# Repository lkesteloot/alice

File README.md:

# Alice website

Hardware projects from the 1990s and our revival and redesign starting in 2015 of that project and projects inspired by it. See the [web page](http://lkesteloot.github.io/alice/).

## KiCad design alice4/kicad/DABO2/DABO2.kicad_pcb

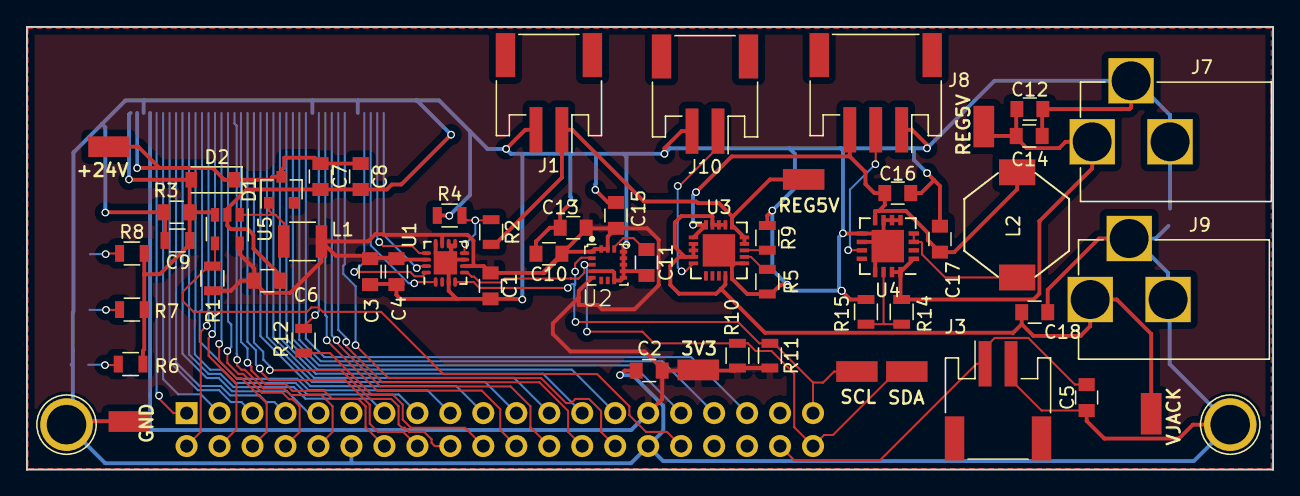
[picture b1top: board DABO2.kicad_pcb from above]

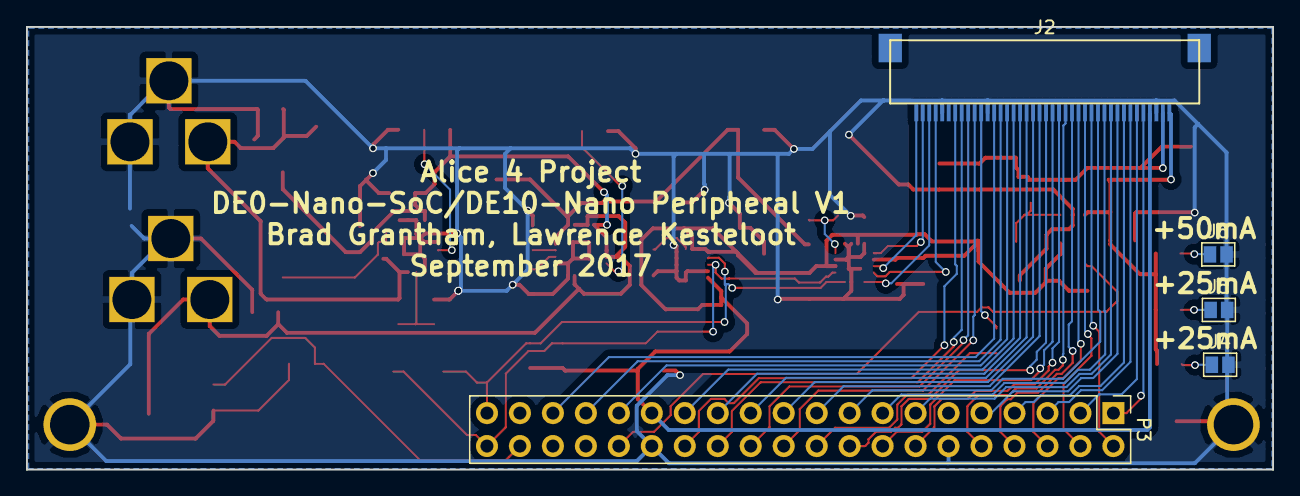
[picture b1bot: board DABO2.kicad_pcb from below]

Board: 2 copper layers, 96.0 x 34.1 mm, 62 parts (5 on the bottom side), 58 nets.

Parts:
C1, C3, C5, C9, C17: .1uF; C_0805
C2, C6, C15, C16, C18: 10uF; C_0805
C4, C7, C8: 1uF; C_0805
C10, C13: 100nF; C_0805
C11: 10nF; C_0805
C12: 2.2uF; C_0805
C14: 100uF; C_0805
D1: BAT54; SOT-23
D2: MM3Z24VT1G; D_SOD-123
HOLE0, HOLE1: MountingHole_2-5mm; 1pin
J1: LIPO; JST_PH_S2B-PH-SM4-TB_02x2.00mm_Angled
J2: LCD; kyocera_6288
J3: HOME; JST_PH_S2B-PH-SM4-TB_02x2.00mm_Angled
J4, J5: +25mA; GS2
J6: +50mA; GS2
J7: 5VOUT; BARREL_JACK
J8: PWRSW; JST_PH_S3B-PH-SM4-TB_03x2.00mm_Angled
J9: 5VIN; BARREL_JACK
J10: THERM; JST_PH_S2B-PH-SM4-TB_02x2.00mm_Angled
L1: 10uH; R_1210
L2: 6.8uH; inductor_8mm_8mm_smt
P3: GPIO0; Pin_Header_Straight_2x20_Pitch2.54mm
R1: 10K; R_0805
R2, R4, R15: 200K; R_0805
R3, R6, R7: 12; R_0805
R5: 100K; R_0805
R8: 6; R_0805
R9: 1K; R_0805
R10, R11: 2.2K; R_0805
R12: 22; R_0805
R14: 1.87M; R_0805
TP1: GND; testpoint_smd_1206
TP2: 3V3; testpoint_smd_1206
TP3: 5VIN; testpoint_smd_1206
TP4: LED-A; testpoint_smd_1206
TP5: LIPO; testpoint_smd_1206
TP6: 5VOUT; testpoint_smd_1206
TP7: SDA; testpoint_smd_1206
TP8: SCL; testpoint_smd_1206
U1: stmpe811; QFN-16-1EP_3x3mm_Pitch0.5mm
U2: l3gd20h
U3: mcp73871; QFN-20-1EP_4x4mm_Pitch0.5mm
U4: tps61090rsar; QFN-16-1EP_4x4mm_Pitch0.65mm
U5: fan5333bsx; SOT-23-5

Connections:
+3V3: C1.1, C2.1, C3.1, C4.1, C6.1, C10.2, C13.1, C15.1, J2.4, L1.1, P3.29, R1.2, R10.2, R11.2, TP2.1, U1.6, U1.11, U1.14, U2.1, U2.5, U2.15, U2.16, U5.5
B0: J2.21, P3.19
B1: J2.22, P3.21
B2: J2.23, P3.23
B3: J2.24, P3.25
B4: J2.25, P3.27
B5: J2.26, P3.31
B6: J2.27, P3.33
B7: J2.28, P3.35
BACKLIGHT_PWM: P3.32, R1.1, U5.4
DATA_ENABLE: J2.34, P3.28
DISPLAY_ON: J2.31, P3.22
G0: J2.13, P3.2
G1: J2.14, P3.4
G2: J2.15, P3.6
G3: J2.16, P3.8
G4: J2.17, P3.10
G5: J2.18, P3.14
G6: J2.19, P3.16
G7: J2.20, P3.18
GND: C1.2, C2.2, C3.2, C4.2, C5.1, C6.2, C7.2, C8.2, C9.2, C10.1, C11.2, C12.2, C13.2, C14.2, C15.2, C16.2, C17.2, C18.2, HOLE0.1, HOLE1.1, J1.2, J2.3, J2.29, J2.36, J3.2, J4.2, J5.2, J6.2, J7.2, J7.3, J8.1, J9.2, J9.3, J10.2, P3.12, P3.30, R3.1, R4.1, R5.1, R9.1, R15.1, TP1.1, U1.3, U1.7, U1.9, U1.10, U1.12, U1.17, U2.4, U2.8, U2.9, U2.10, U2.11, U2.12, U2.13, U3.10, U3.11, U3.21, U4.5, U4.6, U4.7, U4.9, U4.10, U4.13, U4.17, U5.2
HOME: C5.2, J3.1, P3.38
HSYNC: J2.32, P3.24
LCD_CLK: P3.20, R12.2
LED-A: C7.1, C8.1, D1.3, D2.1, J2.2, TP4.1
LED-K: C9.1, D2.2, J2.1, R3.2, R6.2, R7.2, R8.2, U5.3
LIPO: J1.1, R2.2, TP5.1, U3.14, U3.15, U3.16
unnamed: C11.1, U2.14
unnamed: D1.1, L1.2, U5.1
unnamed: J2.30, R12.1
unnamed: J4.1, R6.1
unnamed: J5.1, R7.1
unnamed: J6.1, R8.1
unnamed: J10.1, U3.5
unnamed: L2.2, U4.3, U4.4
unnamed: R2.1, R4.2, U1.8
unnamed: R5.2, U3.12
unnamed: R9.2, U3.13
unnamed: R14.1, R15.2, U4.14
PWREN: J8.2, U4.11
R0: J2.5, P3.1
R1: J2.6, P3.3
R2: J2.7, P3.5
R3: J2.8, P3.7
R4: J2.9, P3.9
R5: J2.10, P3.13
R6: J2.11, P3.15
R7: J2.12, P3.17
REGULATED5V: C12.1, C14.1, J7.1, R14.2, TP6.1, U4.1, U4.15, U4.16
SCL: P3.39, R11.1, TP8.1, U1.4, U2.2
SDA: P3.40, R10.1, TP7.1, U1.5, U2.3
VBAT: C16.1, C17.1, J8.3, L2.1, U3.1, U3.20, U4.8
VJACK: C18.1, J9.1, TP3.1, U3.2, U3.3, U3.4, U3.9, U3.17, U3.18, U3.19
VSYNC: J2.33, P3.26
XL: J2.39, U1.13
XR: J2.37, U1.16
YD: J2.38, U1.1
YU: J2.40, U1.15

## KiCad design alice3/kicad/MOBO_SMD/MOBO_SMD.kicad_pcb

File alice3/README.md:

# Alice III

This is the third model of the Alice machine. It runs a silicon Z80 with
two co-processors: an ARM for keyboard, disk, and serial port, and a Propeller for video.

The 80MHz Propeller has 48K of internal RAM, drives VGA and the 5-pin Aux connector (intended for audio but wired generically to 3 Propeller pins) and thus provides opportunities for video and other experimentation.

The 168MHz STM32F415 ARM Cortex-M4 contains 192K of RAM and is connected to a PS/2 port, an SD card, and a simple UART on a 2-pin header, and has a firmware monitor that can be altered or replaced.

In the `kicad` directory are various schematics and PCBs. The latest is
`MOBO_SMD`, which uses surface mount versions of the parts.

To bring up a new board:

* Power:
    * Use a wall wart to provide micro-USB power. Verify that the D2 LED
      (closest to the switches) is on.  If you have an in-line USB
      current meter, there should be less than 10 mA being initially pulled.
      (More is pulled later when the board is fully brought up.)
* Propeller:
    * Hook up the Prop Plug. The Vss pin should be closest to the corner of
      the board.
    * Run PropellerIDE, load the `video_board/propeller/Main.spin` file,
      and program the EEPROM. After this you should be able to hook up a VGA
      monitor and see the line `Alice 3 GPU firmware`.
    * Remove the Prop Plug.
* Cortex-M4:
    * Connect your computer to the USB jack of the Alice III.
    * Short the header closest to the ARM, labeled "JP1".
    * Hard-reset the board (the push button closest to the LEDs).
    * Wait one second, then remove the jumper.  If you look in your
      USB device list, you should see the STM bootloader.  For example,
      on MacOS X, the output of `system_profiler SPUSBDataType` should
      contain a section similar to:
```
        STM32  BOOTLOADER:

          Product ID: 0xdf11
          Vendor ID: 0x0483  (STMicroelectronics)
          Version: 22.00
          Serial Number: 366A34573335
          Speed: Up to 12 Mb/sec
          Manufacturer: STMicroelectronics
          Location ID: 0x14100000 / 20
          Current Available (mA): 1000
          Current Required (mA): 100
          Extra Operating Current (mA): 0
```
    * In `binaries`, run `sh install_cortex_m4_firmware.sh`.
        * `dfu-util` is a prerequisite.  It can be installed
	  on MacOS (our primary platform) through MacPorts, or you
	  can compile it from the source at
          `git://git.code.sf.net/p/dfu-util/dfu-util`.
    * To interact with the boot monitor:
        * Locate the 2-pin header closest to the MicroSD socket.
          There's no label on this header.
        * Attach a serial transceiver to this header; transmit to the pin
          closest to the ARM, and receive from the other pin.
          E.g. connect FTDI Tx to the pin closer to the ARM and
          FTDI Rx to the pin further from the ARM.
        * Connect to the serial port at 115200 baud.
        * When you hard-reset or power-on the Alice III, you should see
          on the serial port "Alice 3 I/O firmware" followed by the
          firmware build date.
* Z80:
    * Format a MicroSD card for FAT32.
    * Copy `binaries/bootrom.bin`, `binaries/boot.dsk` and `binaries/disks.txt` to the MicroSD card.
    * Install the MicroSD card in the Alice III and power-on or hard-reset the Alice III.

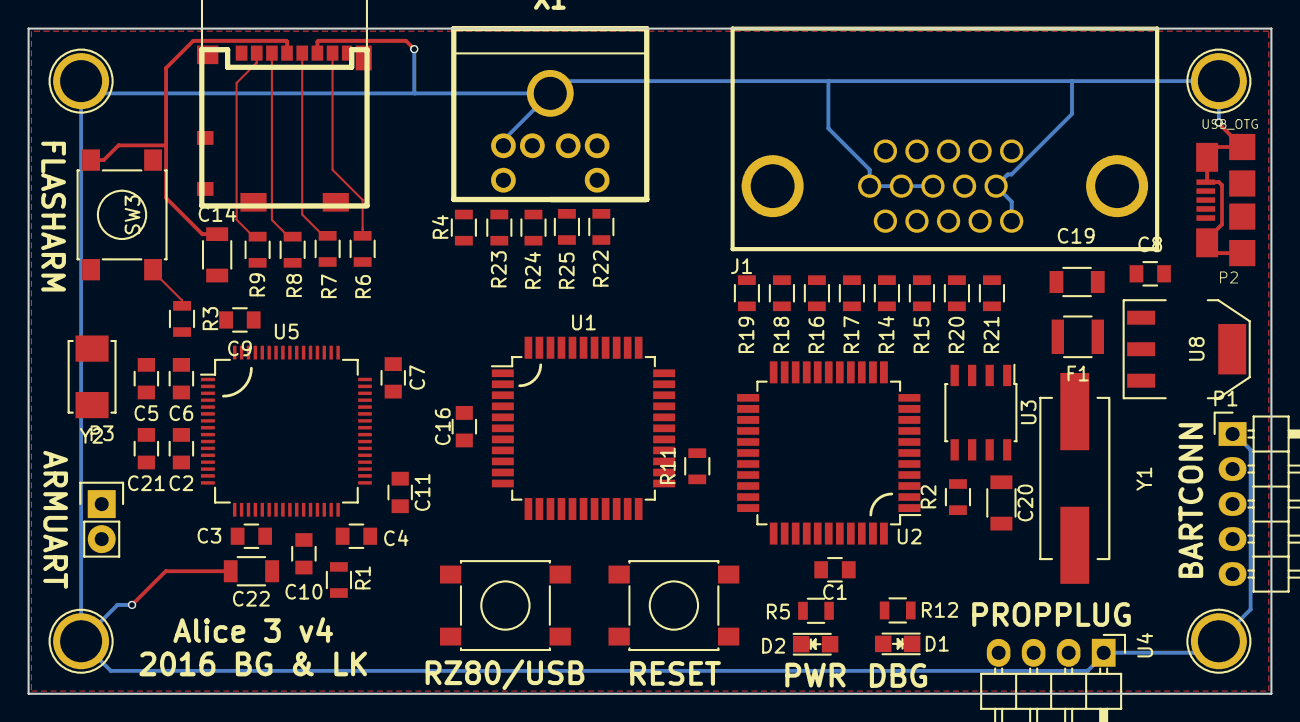
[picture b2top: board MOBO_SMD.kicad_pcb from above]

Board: 2 copper layers, 90.2 x 48.3 mm, 64 parts (0 on the bottom side), 86 nets.

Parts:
C1, C16: 0.1 µF; C_0805
C2, C3, C4, C7, C8, C9: 100nF; C_0805
C5, C6: 22pF; C_0805
C10, C11: 2.2µF; C_0805
C14, C19, C20: 10µF; C_1206
C21: 1µ; C_0805
C22: 4.7µ; C_1206
CON1: MicroSD; microsd_1040310811
D1: DEBUG LED; LED-0805
D2: POWER; LED_0805
F1: F_Small; R_1210
HOLE0, HOLE1, HOLE2, HOLE3: 1pin
J1: VGA; 00JG-DB15HDSOCKET
P1: CONN_01X05; Pin_Header_Angled_1x05
P2: USB_OTG; 10118192-0001LF
P3: UART1; Pin_Header_Straight_1x02
R1, R2, R3, R11: 10k; R_0805
R4: 220; R_0805
R5, R12, R24, R25: 100; R_0805
R6, R7, R8, R9: 68K; R_0805
R14, R16, R18, R20, R21: 240; R_0805
R15, R17, R19: 470; R_0805
R22, R23: 10K; R_0805
SW1: RESET; SW_SPST_PTS645
SW2: SOFT RESET; SW_SPST_PTS645
SW3: FLASH ARM; SW_SPST_PTS645
U1: Z80CPU-SMD; LQFP-44_10x10mm_Pitch0.8mm
U2: Propeller_P8X32A-Q44; LQFP-44_10x10mm_Pitch0.8mm
U3: 24LC256; SOIC-8_3.9x4.9mm_Pitch1.27mm
U4: Propeller_Plug; Pin_Header_Angled_1x04
U5: STM32F415RG; LQFP-64_10x10mm_Pitch0.5mm
U8: LD29080DT33R; SOT-223
X1: MINI_DIN_6; cui-md-60s
Y1: 5 MHz; Crystal_HC49-SD_SMD
Y2: 16MHz; ABM3

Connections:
+3V3: C1.1, C2.2, C3.2, C4.2, C7.2, C9.2, C14.1, C16.1, C20.1, C21.2, C22.2, CON1.4, D2.2, P1.2, R2.1, R6.1, R7.1, R8.1, R9.1, SW2.2, SW3.2, U1.6, U1.12, U1.13, U2.8, U2.18, U2.30, U2.40, U3.8, U5.1, U5.13, U5.19, U5.32, U5.48, U5.64, U8.3
+5V: C8.2, C19.1, F1.2, J1.9, R4.2, R22.2, R23.2, U8.1, X1.4
/IO/CS: CON1.2, R9.2, U5.41
/IO/DI: CON1.3, R8.2, U5.36
/IO/DO: CON1.7, R6.2, U5.35
/IO/SCK: CON1.5, R7.2, U5.34
A0: U1.27, U2.31, U5.8
A1: U1.28, U2.32, U5.9
A2: U1.29, U2.33, U5.10
A3: U1.30, U5.11
A4: U1.31, U5.24
A5: U1.32, U5.25
A6: U1.34, U5.37
A7: U1.35, U2.1, U5.38
A8: U1.36, U5.39
A9: U1.37, U5.40
A10: U1.38, U5.51
A11: U1.40, U5.52
A12: U1.41, U5.53
A13: U1.42, U5.2
A14: U1.43, U5.3
A15: U1.44, U5.4
CLK: U1.1, U2.2
D0: U1.9, U2.19, U5.14
D1: U1.10, U2.20, U5.15
D2: U1.7, U2.21, U5.16
D3: U1.3, U2.22, U5.17
D4: U1.2, U2.23, U5.20
D5: U1.4, U2.24, U5.21
D6: U1.5, U2.25, U5.22
D7: U1.8, U2.26, U5.23
GND: C1.2, C2.1, C3.1, C4.1, C5.2, C6.1, C7.1, C8.1, C9.1, C10.2, C11.2, C14.2, C16.2, C19.2, C20.2, C21.1, C22.1, CON1.6, D1.1, HOLE0.1, HOLE1.1, HOLE2.1, HOLE3.1, J1.5, J1.6, J1.7, J1.8, J1.10, P1.1, P2.5, P2.6, R1.2, R3.2, R5.2, R11.2, SW1.2, U1.26, U2.5, U2.6, U2.17, U2.27, U2.39, U3.1, U3.2, U3.3, U3.4, U3.7, U4.1, U5.12, U5.18, U5.63, U8.2, X1.3, X1.GND
KBD_CLK: R24.1, U5.30
KBD_DATA: R25.1, U5.33
unnamed: C5.1, U5.5, Y2.1
unnamed: C6.2, U5.6, Y2.2
unnamed: C10.1, U5.31
unnamed: C11.1, U5.47
unnamed: D1.2, R12.2
unnamed: D2.1, R5.1
unnamed: F1.1, P2.1
unnamed: J1.1, R18.1, R19.1
unnamed: J1.2, R16.1, R17.1
unnamed: J1.3, R14.1, R15.1
unnamed: J1.13, R21.2
unnamed: J1.14, R20.2
unnamed: P1.3, U2.34
unnamed: P1.4, U2.4
unnamed: P1.5, U2.3
unnamed: P3.1, U5.58
unnamed: P3.2, U5.59
unnamed: R1.1, R12.1, U5.28
unnamed: R2.2, U2.36, U3.5
unnamed: R3.1, SW3.1, U5.60
unnamed: R22.1, R25.2, X1.1
unnamed: R23.1, R24.2, X1.5
unnamed: SW2.1, U5.57
unnamed: U2.28, Y1.1
unnamed: U2.29, Y1.2
unnamed: U2.35, U3.6
unnamed: U2.37, U4.4
unnamed: U2.38, U4.3
USB_DET: R4.1, U5.42
USB_D_N: P2.2, U5.44
USB_D_P: P2.3, U5.45
USB_ID: P2.4, U5.43
VGA_B0: R15.2, U2.11
VGA_B1: R14.2, U2.12
VGA_G0: R17.2, U2.13
VGA_G1: R16.2, U2.14
VGA_HSYNC: R21.1, U2.10
VGA_R0: R19.2, U2.16
VGA_R1: R18.2, U2.15
VGA_VSYNC: R20.1, U2.9
~BUSACK: U1.20, U5.62
~BUSRQ: U1.22, U5.29
~HALT: U1.14, U5.50
~IORQ: U1.16, U2.42, U5.26
~MREQ: U1.15, U5.27
~PROP_READY~: U2.41, U5.46
~RD: U1.18, U2.44, U5.55
~RESET: SW1.1, U2.7, U4.2, U5.7
~RFSH: U1.25, U5.49
~WAIT: U1.21, U5.54
~WR: U1.19, U2.43, U5.56
~Z80_RESET: R11.1, U1.23, U5.61

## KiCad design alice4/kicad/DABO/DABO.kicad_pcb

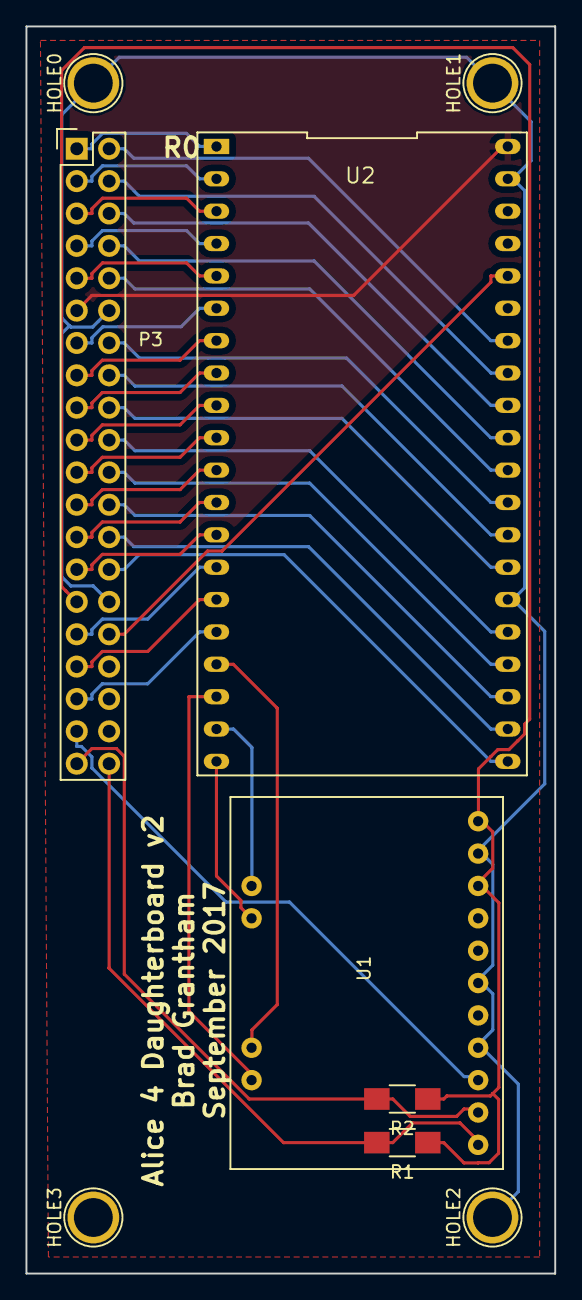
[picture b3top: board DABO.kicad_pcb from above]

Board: 2 copper layers, 41.5 x 97.9 mm, 9 parts (0 on the bottom side), 40 nets.

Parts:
HOLE0, HOLE1, HOLE2, HOLE3: 1pin
P3: CONN_02X20; Pin_Header_Straight_2x20
R1, R2: 3.3; R_1206_HandSoldering
U1: touchscreen_controller; Adafruit_STMPE610
U2: LCDBREAKOUT; DIP-40_1_ELL

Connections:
+3V3: P3.29, R1.1, R2.1, U1.13, U1.15
+5V: P3.11, U2.40
B0: P3.19, U2.9
B1: P3.21, U2.10
B2: P3.23, U2.11
B3: P3.25, U2.12
B4: P3.27, U2.13
B5: P3.31, U2.14
B6: P3.33, U2.15
B7: P3.35, U2.16
BACKLIGHT_PWM: P3.32, U2.36
DATA_ENABLE: P3.28, U2.21
DISPLAY_ON: P3.22, U2.24
G0: P3.2, U2.34
G1: P3.4, U2.33
G2: P3.6, U2.32
G3: P3.8, U2.31
G4: P3.10, U2.30
G5: P3.14, U2.29
G6: P3.16, U2.28
G7: P3.18, U2.27
GND: HOLE0.1, HOLE1.1, HOLE2.1, HOLE3.1, P3.12, P3.30, U1.8, U1.10, U1.14, U2.26, U2.39
HSYNC: P3.24, U2.23
INT: P3.37, U1.7
LCD_CLK: P3.20, U2.25
R0: P3.1, U2.1
R1: P3.3, U2.2
R2: P3.5, U2.3
R3: P3.7, U2.4
R4: P3.9, U2.5
R5: P3.13, U2.6
R6: P3.15, U2.7
R7: P3.17, U2.8
SCL: P3.39, R2.2, U1.6
SDA: P3.40, R1.2, U1.5
VSYNC: P3.26, U2.22
X+: U1.1, U2.19
X-: U1.3, U2.17
Y+: U1.2, U2.20
Y-: U1.4, U2.18

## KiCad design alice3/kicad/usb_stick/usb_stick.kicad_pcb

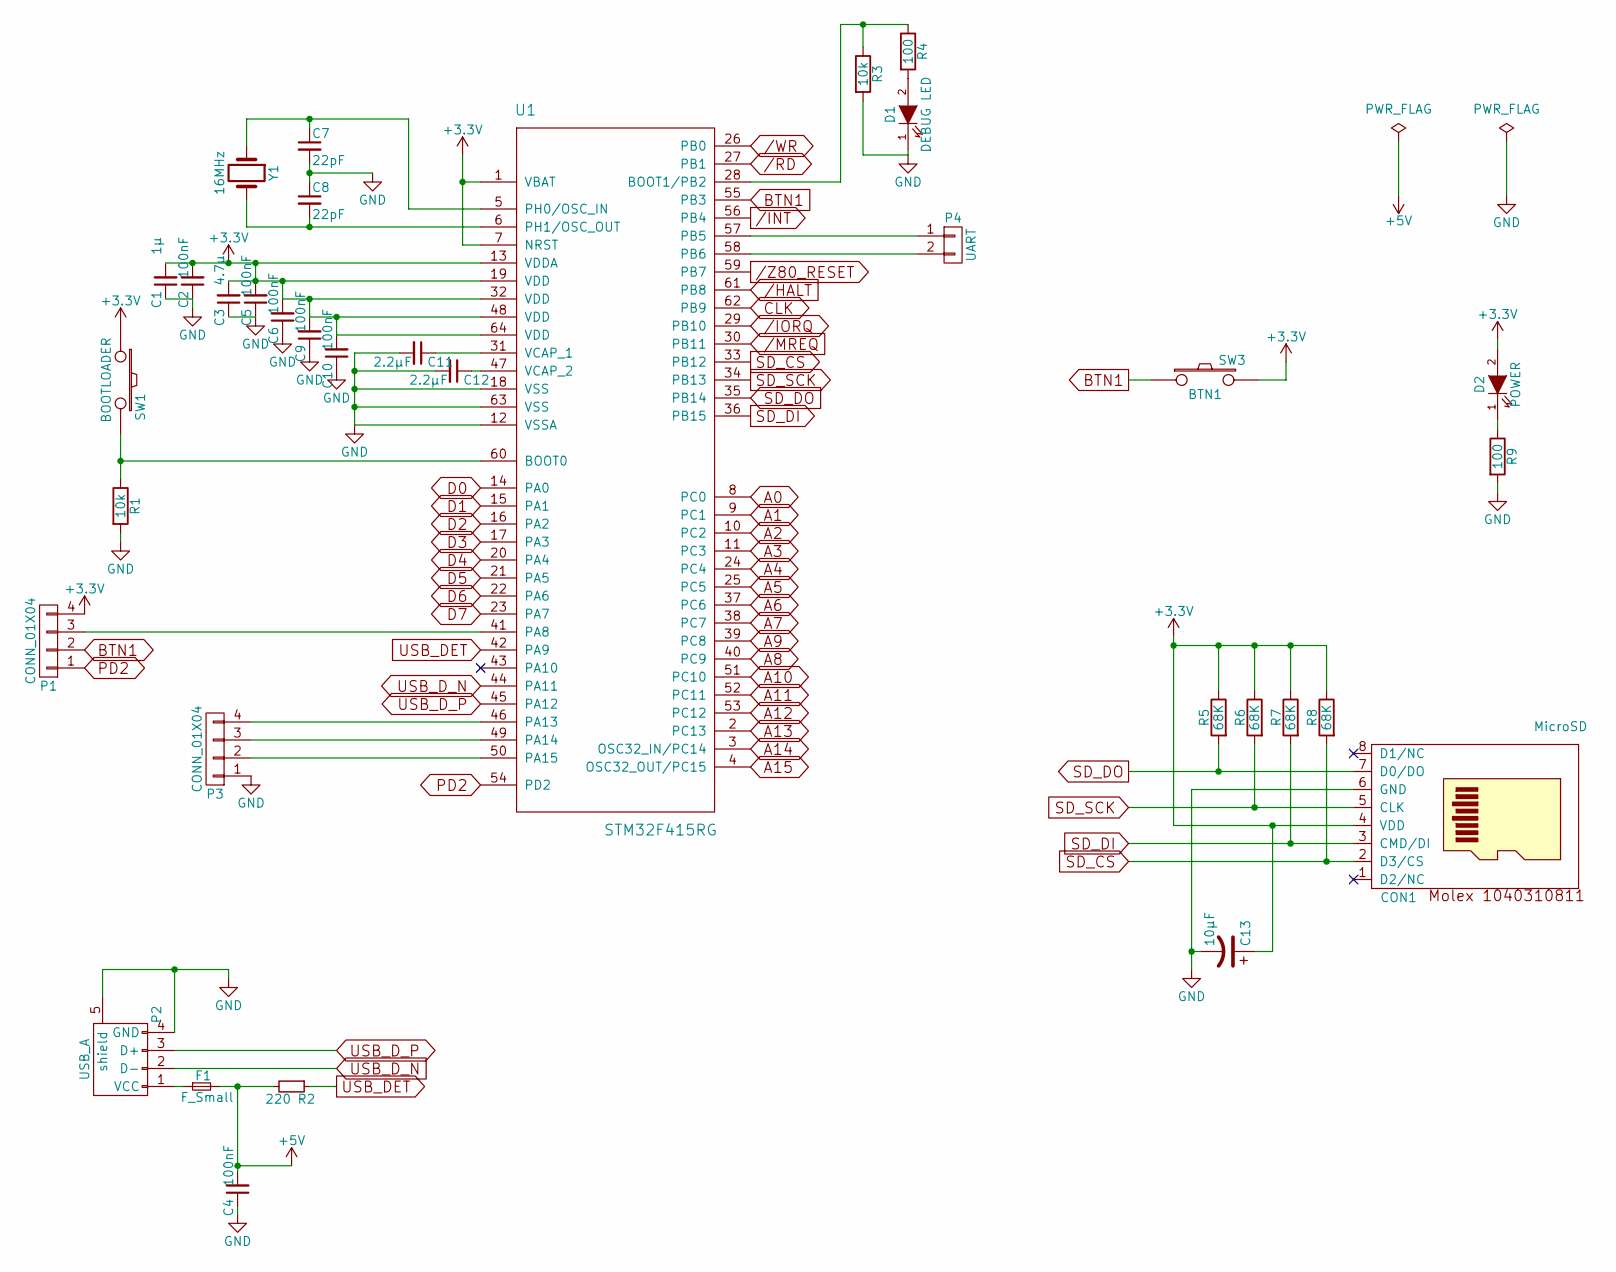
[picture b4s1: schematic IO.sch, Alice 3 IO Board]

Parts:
C1: 1µ; C_0805
C2, C4, C5, C6, C9, C10: 100nF; C_0805
C3: 4.7µ; C_1206
C7, C8: 22pF; C_0805
C11, C12: 2.2µF; C_0805
C13: 10µF; C_1206
CON1: MicroSD; microsd_1040310811
D1: DEBUG LED; LED-0805
D2: POWER; LED_0805
F1: F_Small; R_1210
P1: CONN_01X04; Pin_Header_Straight_1x04
P2: USB_A; usb-PCB
P3: CONN_01X04; Pin_Header_Angled_1x04
P4: UART; Pin_Header_Straight_1x02
R1, R3: 10k; R_0805
R2: 220; R_0805
R4, R9: 100; R_0805
R5, R6, R7, R8: 68K; R_0805
SW1: BOOTLOADER; 00JG-PUSHBUTTON
SW3: BTN1; 00JG-PUSHBUTTON
U1: STM32F415RG; LQFP-64_10x10mm_Pitch0.5mm
Y1: 16MHz; ABM3

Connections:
+5V: C4.2, F1.2, R2.2; also elsewhere on the board
/HALT: U1.61 (PB8); also elsewhere on the board
/INT: U1.56 (PB4); also elsewhere on the board
/IORQ: U1.29 (PB10); also elsewhere on the board
/MREQ: U1.30 (PB11); also elsewhere on the board
/RD: U1.27 (PB1); also elsewhere on the board
/WR: U1.26 (PB0); also elsewhere on the board
/Z80_RESET: U1.59 (PB7); also elsewhere on the board
A0: U1.8 (PC0); also elsewhere on the board
A1: U1.9 (PC1); also elsewhere on the board
A2: U1.10 (PC2); also elsewhere on the board
A3: U1.11 (PC3); also elsewhere on the board
A4: U1.24 (PC4); also elsewhere on the board
A5: U1.25 (PC5); also elsewhere on the board
A6: U1.37 (PC6); also elsewhere on the board
A7: U1.38 (PC7); also elsewhere on the board
A8: U1.40 (PC9); also elsewhere on the board
A9: U1.39 (PC8); also elsewhere on the board
A10: U1.51 (PC10); also elsewhere on the board
A11: U1.52 (PC11); also elsewhere on the board
A12: U1.53 (PC12); also elsewhere on the board
A13: U1.2 (PC13); also elsewhere on the board
A14: U1.3 (OSC32_IN/PC14); also elsewhere on the board
A15: U1.4 (OSC32_OUT/PC15); also elsewhere on the board
BTN1: P1.2, SW3.1, U1.55 (PB3)
CLK: U1.62 (PB9); also elsewhere on the board
D0: U1.14 (PA0); also elsewhere on the board
D1: U1.15 (PA1); also elsewhere on the board
D2: U1.16 (PA2); also elsewhere on the board
D3: U1.17 (PA3); also elsewhere on the board
D4: U1.20 (PA4); also elsewhere on the board
D5: U1.21 (PA5); also elsewhere on the board
D6: U1.22 (PA6); also elsewhere on the board
D7: U1.23 (PA7); also elsewhere on the board
GND: C1.1, C2.1, C3.1, C4.1, C5.1, C6.1, C7.2, C8.1, C9.1, C10.1, C11.2, C12.2, C13.2, CON1.6 (GND), D1.1 (K), P2.4 (GND), P2.5 (shield), P3.1, R1.2, R3.2, R9.2, U1.12 (VSSA), U1.18 (VSS), U1.63 (VSS); also elsewhere on the board
unnamed: C7.1, U1.5 (PH0/OSC_IN), Y1.1
unnamed: C8.2, U1.6 (PH1/OSC_OUT), Y1.2
unnamed: C11.1, U1.31 (VCAP_1)
unnamed: C12.1, U1.47 (VCAP_2)
unnamed: D1.2 (A), R4.2
unnamed: D2.1 (K), R9.1
unnamed: F1.1, P2.1 (VCC)
unnamed: P1.3, U1.41 (PA8)
unnamed: P3.2, U1.50 (PA15)
unnamed: P3.3, U1.49 (PA14)
unnamed: P3.4, U1.46 (PA13)
unnamed: P4.1, U1.57 (PB5)
unnamed: P4.2, U1.58 (PB6)
unnamed: R1.1, SW1.2, U1.60 (BOOT0)
unnamed: R3.1, R4.1, U1.28 (BOOT1/PB2)
PD2: P1.1, U1.54 (PD2)
SD_CS: CON1.2 (D3/CS), R8.2, U1.33 (PB12)
SD_DI: CON1.3 (CMD/DI), R7.2, U1.36 (PB15)
SD_DO: CON1.7 (D0/DO), R5.2, U1.35 (PB14)
SD_SCK: CON1.5 (CLK), R6.2, U1.34 (PB13)
USB_DET: R2.1, U1.42 (PA9)
USB_D_N: P2.2 (D-), U1.44 (PA11)
USB_D_P: P2.3 (D+), U1.45 (PA12)

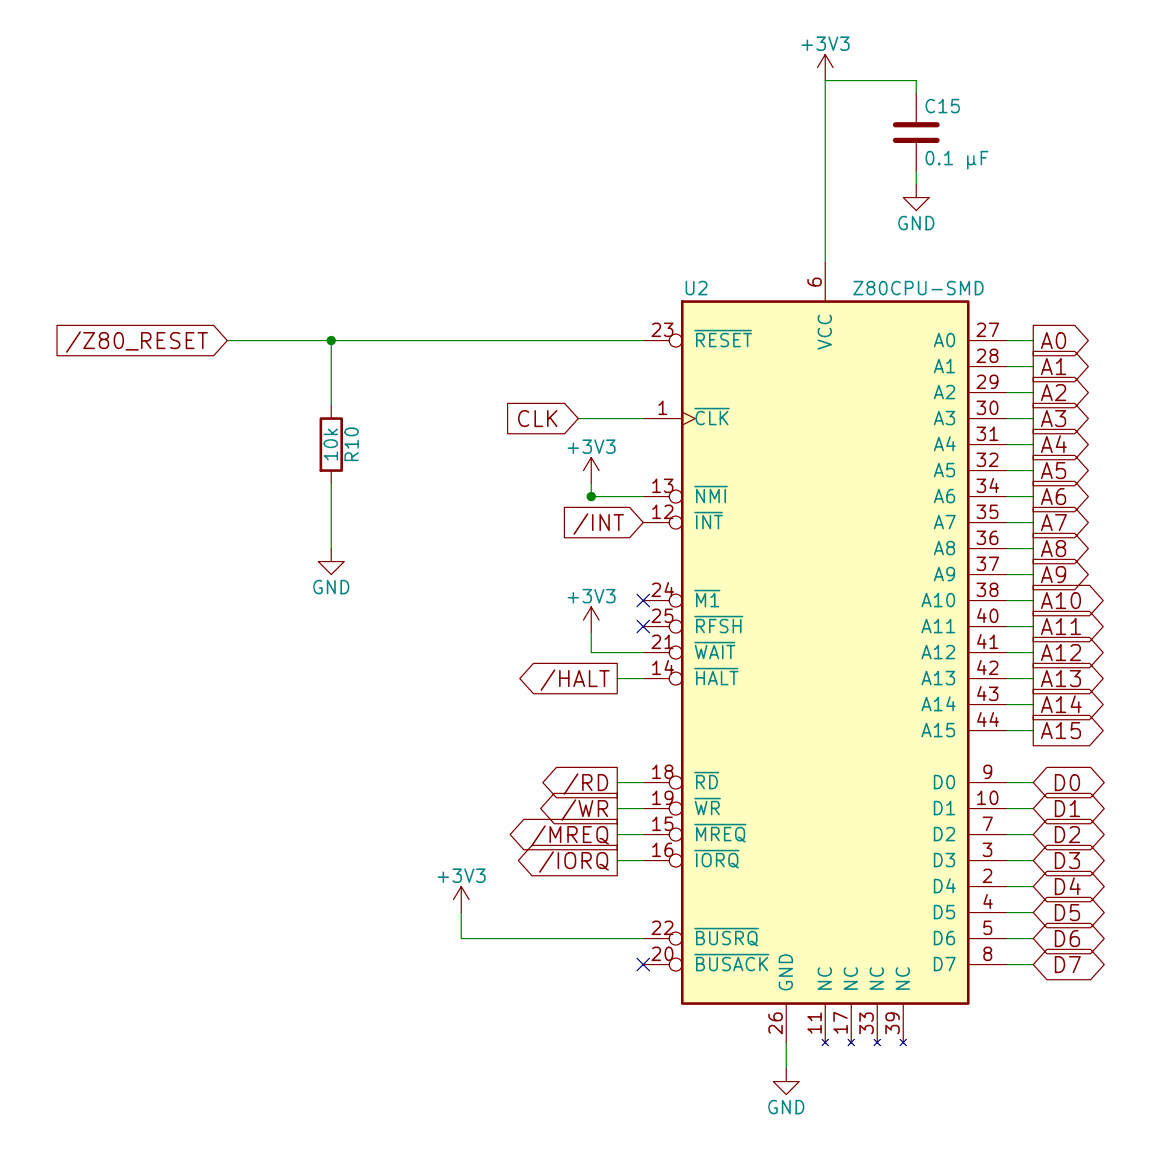
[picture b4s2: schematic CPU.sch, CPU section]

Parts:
C15: 0.1 µF; C_0805
R10: 10k; R_0805
U2: Z80CPU-SMD; LQFP-44_10x10mm_Pitch0.8mm

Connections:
/HALT: U2.14 (~HALT~); also elsewhere on the board
/INT: U2.12 (~INT~); also elsewhere on the board
/IORQ: U2.16 (~IORQ~); also elsewhere on the board
/MREQ: U2.15 (~MREQ~); also elsewhere on the board
/RD: U2.18 (~RD~); also elsewhere on the board
/WR: U2.19 (~WR~); also elsewhere on the board
/Z80_RESET: R10.1, U2.23 (~RESET~); also elsewhere on the board
A0: U2.27 (A0); also elsewhere on the board
A1: U2.28 (A1); also elsewhere on the board
A2: U2.29 (A2); also elsewhere on the board
A3: U2.30 (A3); also elsewhere on the board
A4: U2.31 (A4); also elsewhere on the board
A5: U2.32 (A5); also elsewhere on the board
A6: U2.34 (A6); also elsewhere on the board
A7: U2.35 (A7); also elsewhere on the board
A8: U2.36 (A8); also elsewhere on the board
A9: U2.37 (A9); also elsewhere on the board
A10: U2.38 (A10); also elsewhere on the board
A11: U2.40 (A11); also elsewhere on the board
A12: U2.41 (A12); also elsewhere on the board
A13: U2.42 (A13); also elsewhere on the board
A14: U2.43 (A14); also elsewhere on the board
A15: U2.44 (A15); also elsewhere on the board
CLK: U2.1 (~CLK~); also elsewhere on the board
D0: U2.9 (D0); also elsewhere on the board
D1: U2.10 (D1); also elsewhere on the board
D2: U2.7 (D2); also elsewhere on the board
D3: U2.3 (D3); also elsewhere on the board
D4: U2.2 (D4); also elsewhere on the board
D5: U2.4 (D5); also elsewhere on the board
D6: U2.5 (D6); also elsewhere on the board
D7: U2.8 (D7); also elsewhere on the board
GND: C15.2, R10.2, U2.26 (GND); also elsewhere on the board

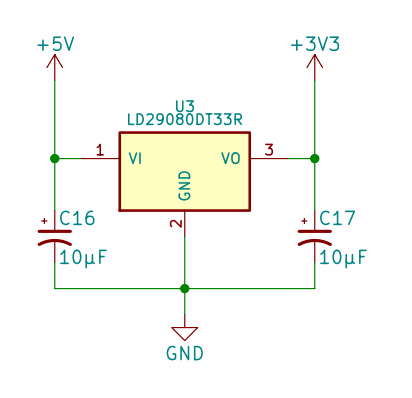
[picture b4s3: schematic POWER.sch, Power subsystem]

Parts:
C16, C17: 10µF; C_1206
U3: LD29080DT33R; SOT-223

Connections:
+5V: C16.1, U3.1 (VI); also elsewhere on the board
GND: C16.2, C17.2, U3.2 (GND); also elsewhere on the board

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
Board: 4 copper layers, 39 parts (13 on the bottom side), 58 nets, no tracks yet.

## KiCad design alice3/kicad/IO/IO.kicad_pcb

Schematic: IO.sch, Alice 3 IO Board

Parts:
C1: 22µF; C_Radial_D5_L11_P2
C2: 470µF; C_Radial_D13_L25_P5
CON1: SD_Card; SD_Card_Receptacle
HEART1: LED; LED-5MM
INFO1: LED; LED-5MM
PANIC1: LED; LED-5MM
R0, R1, R2, R3: 68K; Resistor_Horizontal_RM10mm
R4, R5, R6: 220; Resistor_Horizontal_RM10mm
U1: MiniM4-D40; DIP-40_W15.24mm
U2, U3, U4, U5: LEVELCONVERTER; LEVELCONV
U6: Alice_3_bus; Pin_Header_Straight_2x10
U7: DFROBOT_FTDI_BASIC; FTDIBASIC
U8: LM2937-3.3; TO-220
X1: MINI_DIN_6; Mini_din6

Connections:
+3V3: C1.1, C2.1, CON1.4 (VDD), R0.1, R1.1, R2.1, R3.1, U1.1 (MCLR), U1.11 (Vdd), U1.32 (Vdd), U2.3 (LVdd), U3.3 (LVdd), U4.3 (LVdd), U5.3 (LVdd), U8.3
+5V: U2.10 (HVdd), U3.10 (HVdd), U4.10 (HVdd), U5.10 (HVdd), U6.2 (5V), U6.10 (5V), U8.1, X1.5
//INT: U1.20 (PB1), U5.1 (LV1)
//INT.5v: U5.12 (HV1), U6.3 (/INT)
//IORQ: U1.6 (PC0), U4.1 (LV1)
//IORQ.5v: U4.12 (HV1), U6.9 (/IORQ)
//M1: U1.33 (PC5), U5.6 (LV4)
//M1.5v: U5.7 (HV4), U6.6 (/M1)
//RD: U1.8 (PC1), U4.2 (LV2)
//RD.5v: U4.11 (HV2), U6.7 (/RD)
//RESET: U1.19 (PB0), U5.2 (LV2)
//RESET.5v: U5.11 (HV2), U6.4 (/RESET)
//WAIT: U1.15 (PC9), U5.5 (LV3)
//WAIT.5v: U5.8 (HV3), U6.5 (/WAIT)
//WR: U1.9 (PC2), U4.5 (LV3)
//WR.5v: U4.8 (HV3), U6.8 (/WR)
/A7: U1.34 (PC4), U4.6 (LV4)
/A7.5v: U4.7 (HV4), U6.19 (A7)
/CS: CON1.1 (CD/DAT3), R0.2, U1.10 (PA8)
/D0: U1.2 (PA0), U2.1 (LV1)
/D0.5v: U2.12 (HV1), U6.11 (D0)
/D1: U1.3 (PA1), U2.2 (LV2)
/D1.5v: U2.11 (HV2), U6.12 (D1)
/D2: U1.4 (PA2), U2.5 (LV3)
/D2.5v: U2.8 (HV3), U6.13 (D2)
/D3: U1.5 (PA3), U2.6 (LV4)
/D3.5v: U2.7 (HV4), U6.14 (D3)
/D4: U1.37 (PA4), U3.1 (LV1)
/D4.5v: U3.12 (HV1), U6.15 (D4)
/D5: U1.38 (PA5), U3.2 (LV2)
/D5.5v: U3.11 (HV2), U6.16 (D5)
/D6: U1.40 (PA6), U3.5 (LV3)
/D6.5v: U3.8 (HV3), U6.17 (D6)
/D7: U1.39 (PA7), U3.6 (LV4)
/D7.5v: U3.7 (HV4), U6.18 (D7)
/DI: CON1.2 (CMD), R1.2, U1.24 (PB15)
/DO: CON1.7 (DAT0), R3.2, U1.23 (PB14)
/SCK: CON1.5 (CLK), R2.2, U1.18 (PB13)
GND: C1.2, C2.2, CON1.3 (VSS), CON1.6 (VSS), R4.2, R5.2, R6.2, U1.12 (Vss), U1.31 (Vss), U2.4 (GND), U2.9 (GND), U3.4 (GND), U3.9 (GND), U4.4 (GND), U4.9 (GND), U5.4 (GND), U5.9 (GND), U6.1 (GND), U6.20 (GND), U7.3, U7.10, U8.2, X1.3
unnamed: HEART1.1, R6.1
unnamed: HEART1.2, U1.30 (PA15)
unnamed: INFO1.1, R4.1
unnamed: INFO1.2, U1.16 (PB4)
unnamed: PANIC1.1, R5.1
unnamed: PANIC1.2, U1.17 (PB5)
unnamed: U1.7 (PB12), X1.1
unnamed: U1.25 (PB6), U7.5
unnamed: U1.26 (PB7), U7.9
unnamed: U1.27 (PB11), X1.6

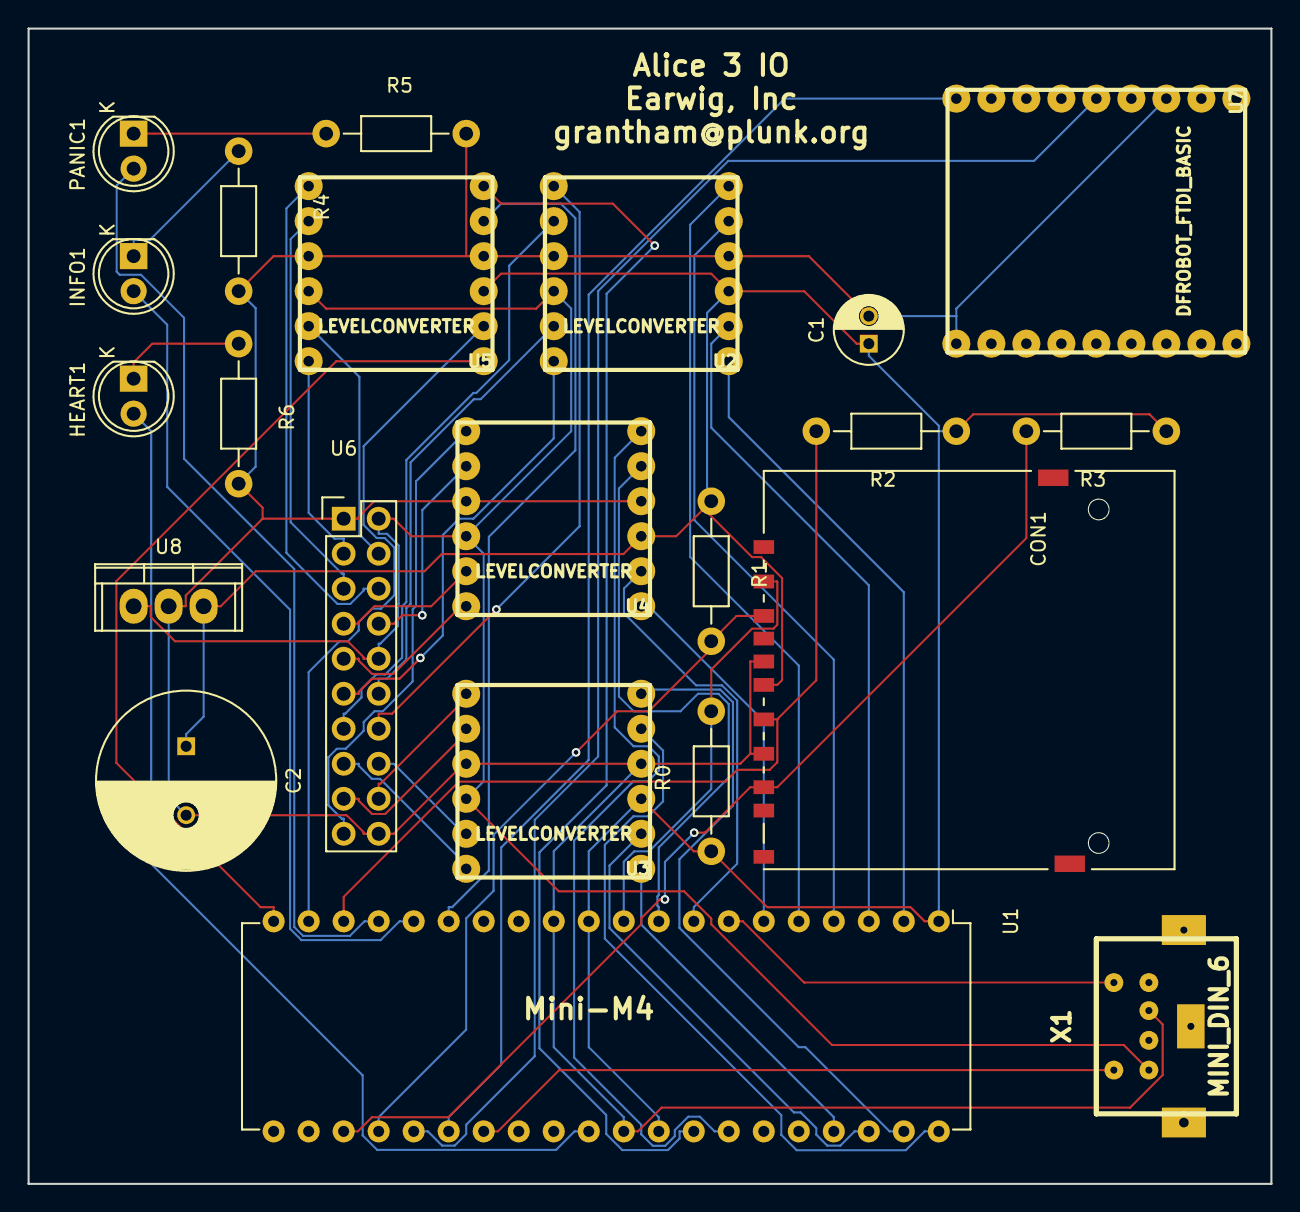
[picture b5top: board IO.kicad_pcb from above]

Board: 2 copper layers, 90.2 x 83.8 mm, 22 parts (0 on the bottom side), 49 nets.

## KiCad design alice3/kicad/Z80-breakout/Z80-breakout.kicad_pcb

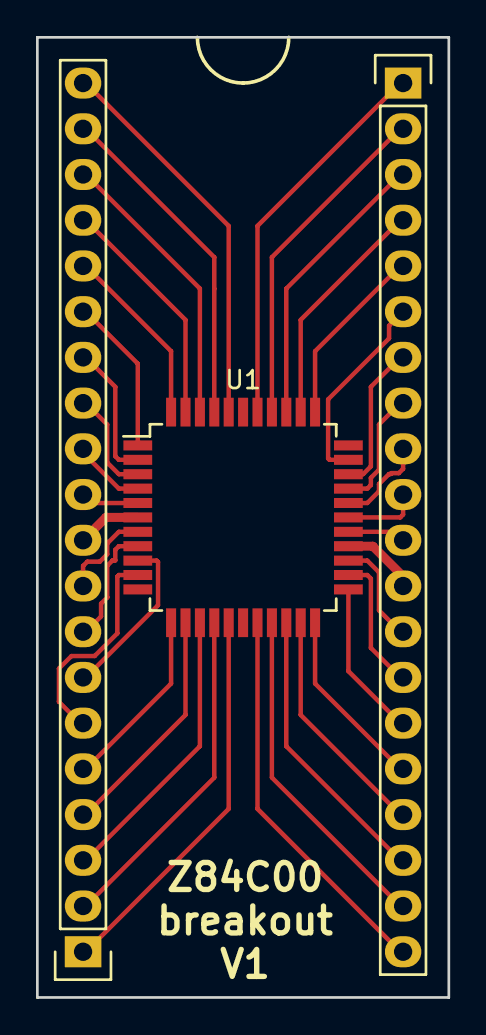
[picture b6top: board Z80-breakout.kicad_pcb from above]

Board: 2 copper layers, 22.9 x 53.3 mm, 3 parts (0 on the bottom side), 40 nets.

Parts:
P1, P2: CONN_01X20; Pin_Header_Straight_1x20
U1: Z80CPU-SMD; LQFP-44_10x10mm_Pitch0.8mm

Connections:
/A0: P2.11, U1.27
/A1: P2.10, U1.28
/A2: P2.9, U1.29
/A3: P2.8, U1.30
/A4: P2.7, U1.31
/A5: P2.6, U1.32
/A6: P2.5, U1.34
/A7: P2.4, U1.35
/A8: P2.3, U1.36
/A9: P2.2, U1.37
/A10: P2.1, U1.38
/A11: P1.20, U1.40
/A12: P1.19, U1.41
/A13: P1.18, U1.42
/A14: P1.17, U1.43
/A15: P1.16, U1.44
/D0: P1.7, U1.9
/D1: P1.6, U1.10
/D2: P1.9, U1.7
/D3: P1.13, U1.3
/D4: P1.14, U1.2
/D5: P1.12, U1.4
/D6: P1.11, U1.5
/D7: P1.8, U1.8
/GND: P2.12, U1.26
/VCC: P1.10, U1.6
/~BUSACK~: P2.18, U1.20
/~BUSRQ~: P2.16, U1.22
/~CLK~: P1.15, U1.1
/~HALT~: P1.3, U1.14
/~INT~: P1.5, U1.12
/~IORQ~: P1.1, U1.16
/~M1~: P2.14, U1.24
/~MREQ~: P1.2, U1.15
/~NMI~: P1.4, U1.13
/~RD~: P2.20, U1.18
/~RESET~: P2.15, U1.23
/~RFSH~: P2.13, U1.25
/~WAIT~: P2.17, U1.21
/~WR~: P2.19, U1.19

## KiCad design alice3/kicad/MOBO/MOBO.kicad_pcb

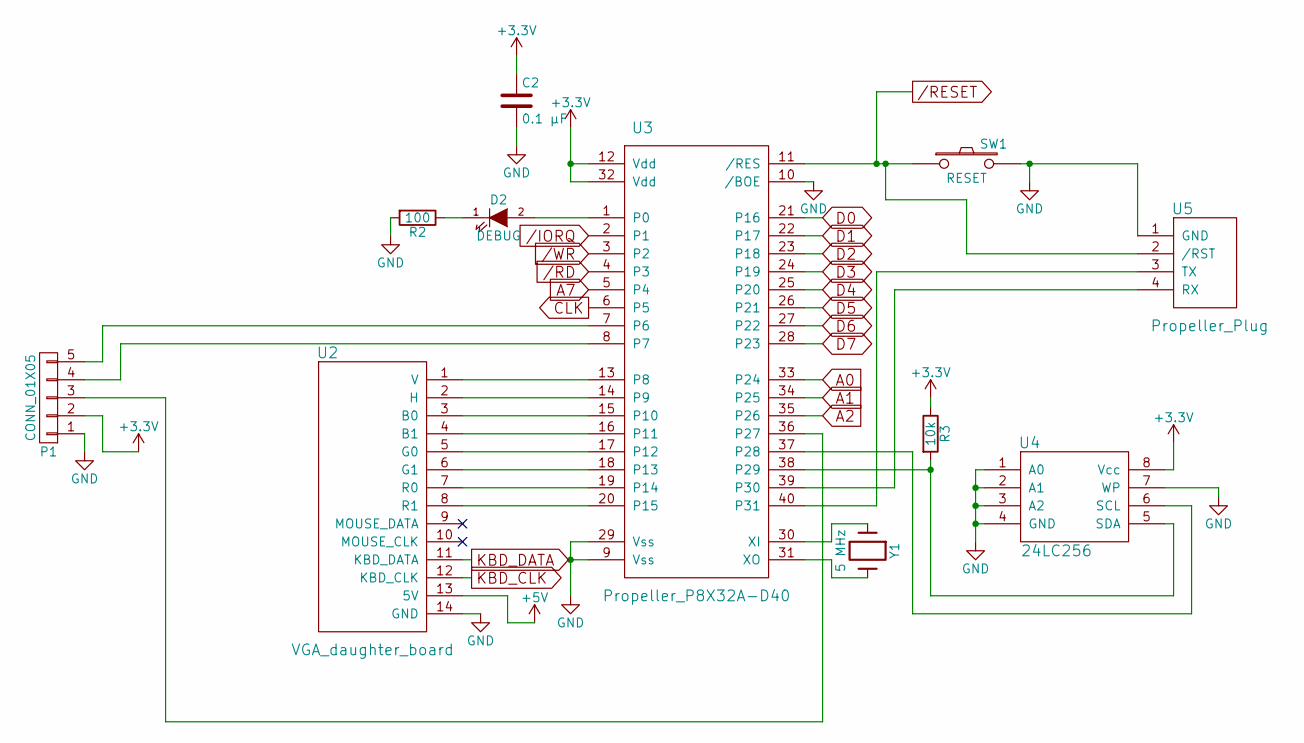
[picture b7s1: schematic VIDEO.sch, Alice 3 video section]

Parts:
C2: 0.1 µF; C_Disc_D6_P5
D2: DEBUG; LED-5MM
P1: CONN_01X05; Pin_Header_Angled_1x05
R2: 100; Resistor_Horizontal_RM10mm
R3: 10k; Resistor_Horizontal_RM10mm
SW1: RESET; SW_PUSH_SMALL
U2: VGA_daughter_board; Pin_Header_Straight_1x14
U3: Propeller_P8X32A-D40; DIP-40_W15.24mm
U4: 24LC256; DIP-8_W7.62mm
U5: Propeller_Plug; Pin_Header_Angled_1x04
Y1: 5 MHz; Crystal_HC50-U_Vertical

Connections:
+5V: U2.13 (5V); also elsewhere on the board
/IORQ: U3.2 (P1); also elsewhere on the board
/RD: U3.4 (P3); also elsewhere on the board
/RESET: SW1.1, U3.11 (/RES), U5.2 (/RST); also elsewhere on the board
/WR: U3.3 (P2); also elsewhere on the board
A0: U3.33 (P24); also elsewhere on the board
A1: U3.34 (P25); also elsewhere on the board
A2: U3.35 (P26); also elsewhere on the board
A7: U3.5 (P4); also elsewhere on the board
CLK: U3.6 (P5); also elsewhere on the board
D0: U3.21 (P16); also elsewhere on the board
D1: U3.22 (P17); also elsewhere on the board
D2: U3.23 (P18); also elsewhere on the board
D3: U3.24 (P19); also elsewhere on the board
D4: U3.25 (P20); also elsewhere on the board
D5: U3.26 (P21); also elsewhere on the board
D6: U3.27 (P22); also elsewhere on the board
D7: U3.28 (P23); also elsewhere on the board
GND: C2.2, P1.1, R2.2, SW1.2, U2.14 (GND), U3.9 (Vss), U3.10 (/BOE), U3.29 (Vss), U4.1 (A0), U4.2 (A1), U4.3 (A2), U4.4 (GND), U4.7 (WP), U5.1 (GND); also elsewhere on the board
KBD_CLK: U2.12 (KBD_CLK); also elsewhere on the board
KBD_DATA: U2.11 (KBD_DATA); also elsewhere on the board
unnamed: D2.1 (K), R2.1
unnamed: D2.2 (A), U3.1 (P0)
unnamed: P1.3, U3.36 (P27)
unnamed: P1.4, U3.8 (P7)
unnamed: P1.5, U3.7 (P6)
unnamed: R3.2, U3.38 (P29), U4.5 (SDA)
unnamed: U2.1 (V), U3.13 (P8)
unnamed: U2.2 (H), U3.14 (P9)
unnamed: U2.3 (B0), U3.15 (P10)
unnamed: U2.4 (B1), U3.16 (P11)
unnamed: U2.5 (G0), U3.17 (P12)
unnamed: U2.6 (G1), U3.18 (P13)
unnamed: U2.7 (R0), U3.19 (P14)
unnamed: U2.8 (R1), U3.20 (P15)
unnamed: U3.30 (XI), Y1.1
unnamed: U3.31 (XO), Y1.2
unnamed: U3.37 (P28), U4.6 (SCL)
unnamed: U3.39 (P30), U5.4 (RX)
unnamed: U3.40 (P31), U5.3 (TX)

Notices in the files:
alice3/io_board/minim4/STM32Cube4/stm32f4xx_hal_gpio.c:
© COPYRIGHT(c) 2015 STMicroelectronics
(C) COPYRIGHT STMicroelectronics *****END OF FILE
